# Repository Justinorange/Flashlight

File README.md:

# 🔦 [Cheap Strong Flashlight]

A high-performance, flashlight project. This design prioritizes cheap high power flashlight creation with a **single-layer PCB** layout, making it cost effective.

---

## 🛠 Technical Specifications

This project is engineered for [e.g., high brightness/long battery life]. By using a single-layer design, we simplify the manufacturing process while maintaining robust electrical paths.

* **PCB Layers:** 1 Layer (Single-sided)
* **Material:** [Recomended Aluminum (or copper $$$) PCB for heat dissipation]
* **LED Count:** [10]
* **LED Type:** [CREE JU7070 K Series (I used JU7070BWT-K-B40ED0000-N0000001)]
* **Drive Current:** [0-1200 mA depending on the voltage (700 mA at 11.8 volts)]
* **Input Voltage:** [10.5-12.4 Volts (optimal is 11.8 V to not release the smoke)]
* **Power:** [With 10 LEDs 0-148.8 W (82.6 W at 11.8 V)]

---

## 📐 Hardware Design

### PCB Layout
The board is designed with large solder pours to handle the current requirements of high-power LEDs and to reduce voltage drop across the circuit.

* **Substrate:** Aluminum-core PCB is highly recommended if running the LEDs at maximum brightness to prevent things from getting too toasty.
* **Solder Mask:** [I chose white (it's the cheapest option on JLC for aluminum)]

### Bill of Materials (BOM)

| Component | Type | Quantity | Notes |
| :--- | :--- | :--- | :--- |
| **LED** | [JU7070BWT-K-B40ED0000-N0000001] | [10] | [Color Temp, e.g., 5000K] |
| **Resistor** | [Not used] | [0] | Current limiting |
| **Switch** | [Insert Type] | 1 | [e.g., Reverse clicky] |
| **Battery** | [DCB 120] | 1 | [Had cheap Dewalt batteries laying around] |
[**NOTE ON BATTERY: MAKE SURE THAT YOU CEHCK YOUR INPUT IS AROUND 12V (11.8 V is what you should aim for the higher you go, the more heat you make)**]
---

## 🚀 Assembly Instructions

1.  **Fabrication:** Export the Gerber files located in `/fabrication` and send them to your preferred PCB manufacturer.
2.  **Solder Components:** * Apply solder paste or flux to the pads.
    * Place the LEDs, ensuring correct polarity (Anode vs. Cathode).
    * Use a reflow plate (recommended for Aluminum PCBs) or a soldering iron.
3.  **Housing:** Fit the PCB into the [Insert Housing/Enclosure Name]. Ensure the LEDs align with the optics/reflector.
4.  **Testing:** Power the device using a limited current source first to ensure there are no shorts.

---

## 📂 Project Structure

* `/hardware` - KiCad design files.
* `/fabrication` - Ready-to-order Gerber files.
* `/enclosure` - 3D printable files (.STL) for the flashlight body.
* `/docs` - Datasheets for LEDs and components.

---

## ⚖️ License
This project is licensed under the [MIT License](LICENSE).

---

## 🤝 Contributing
If you know best practices for thermal vias and stuff like that. Feel free to contact me, I want to learn how to do them.

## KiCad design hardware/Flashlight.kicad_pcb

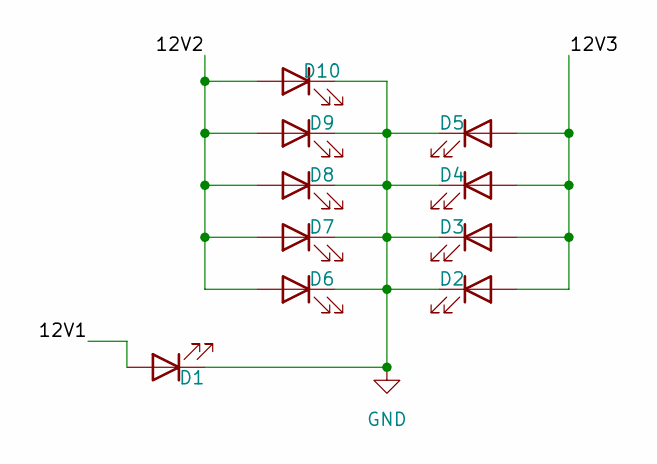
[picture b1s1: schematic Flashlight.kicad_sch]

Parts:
D1, D2, D3, D4, D5, D6, D7, D8, D9, D10: LED; CREE_JU7070B_K

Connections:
/12V1: D1.2 (A)
/12V2: D6.2 (A), D7.2 (A), D8.2 (A), D9.2 (A), D10.2 (A)
/12V3: D2.2 (A), D3.2 (A), D4.2 (A), D5.2 (A)
GND: D1.1 (K), D2.1 (K), D3.1 (K), D4.1 (K), D5.1 (K), D6.1 (K), D7.1 (K), D8.1 (K), D9.1 (K), D10.1 (K)

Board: 2 copper layers, 10 parts (0 on the bottom side), 3 nets, no tracks yet.

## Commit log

2026-01-18 Added schematics
2026-01-18 Finalized Kicad PCB Design
2026-01-18 Changed some PCB things
2026-01-19 2SidedBoard
2026-01-19 Made the PCB one Sided
2026-01-19 Small fixes
2026-01-19 More small changes
2026-01-20 Initialize README for flashlight project
    Add README with project details and assembly instructions
2026-01-21 Removed vias
2026-02-04 Update project name and contribution
    Updated project name and improved contributing section.
2026-02-04 added some docs
